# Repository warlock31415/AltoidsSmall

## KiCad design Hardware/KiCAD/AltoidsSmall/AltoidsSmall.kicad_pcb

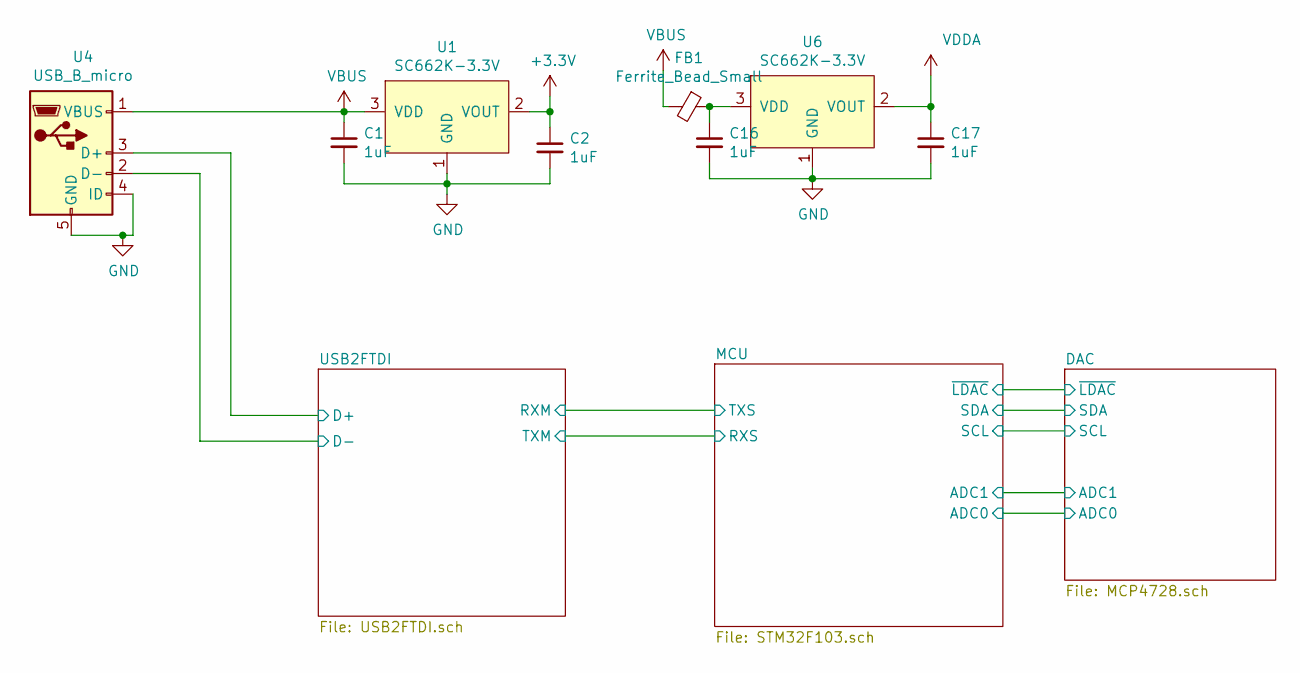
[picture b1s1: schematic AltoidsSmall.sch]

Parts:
C1, C2, C16, C17: 1uF; C_0603_1608Metric_Pad1.05x0.95mm_HandSolder
FB1: Ferrite_Bead_Small; C_0805_2012Metric; Digikey 490-5229-1-ND
U1, U6: SC662K-3.3V; SOT-23
U4: USB_B_micro; USB_Micro-B_PCB

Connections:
/USB2FTDI/D+: U4.3 (D+); also elsewhere on the board
/USB2FTDI/D-: U4.2 (D-); also elsewhere on the board
GND: C1.2, C2.2, C16.2, C17.2, U1.1 (GND), U4.4 (ID), U4.5 (GND), U6.1 (GND); also elsewhere on the board
unnamed: C16.1, FB1.1, U6.3 (VDD)
VBUS: C1.1, FB1.2, U1.3 (VDD), U4.1 (VBUS); also elsewhere on the board
VDDA: C17.1, U6.2 (VOUT); also elsewhere on the board

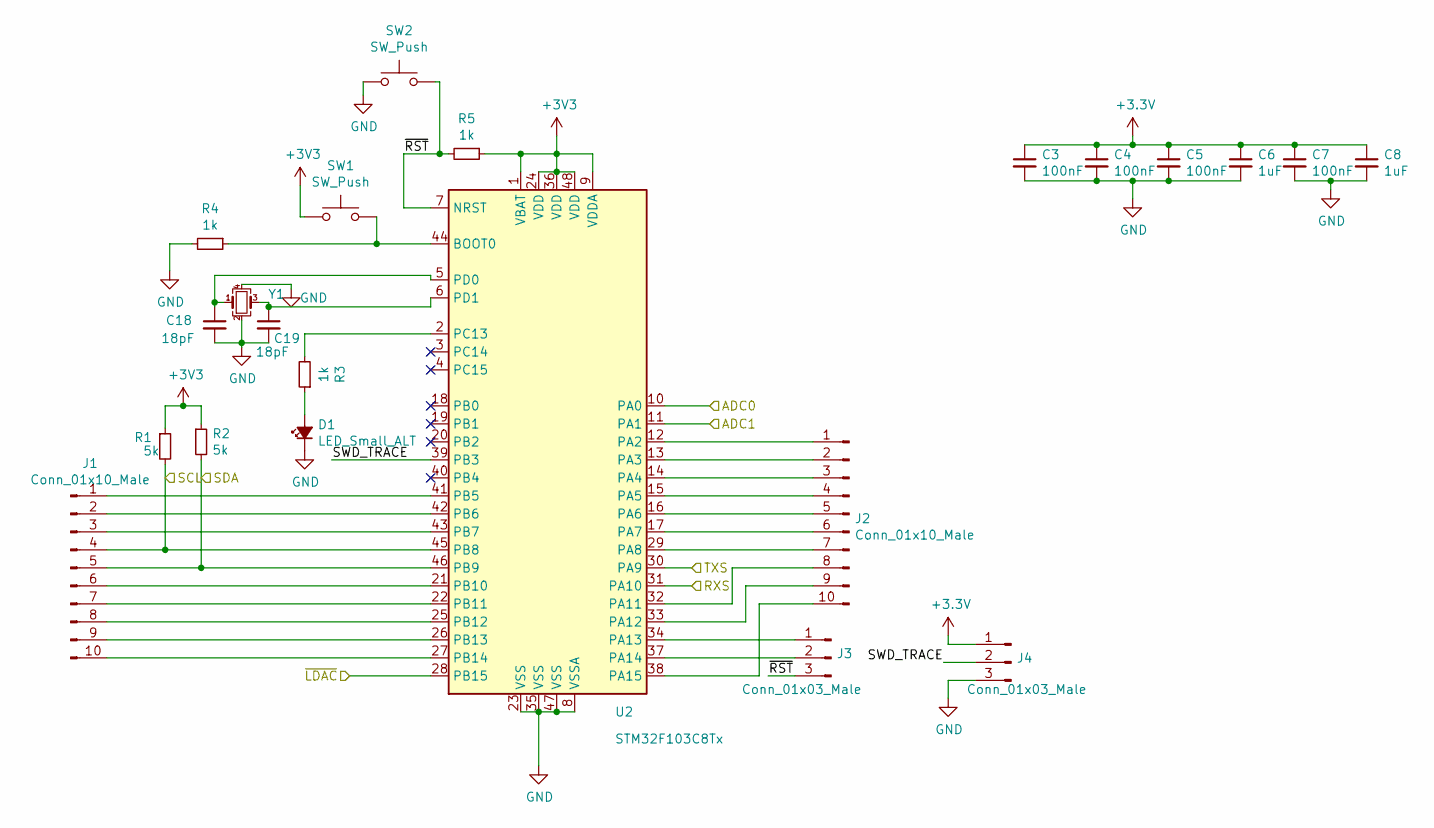
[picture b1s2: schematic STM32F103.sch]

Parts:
C3, C4, C5, C7: 100nF; C_0603_1608Metric_Pad1.05x0.95mm_HandSolder; Digikey 1276-CL10B104KB8VPJCCT-ND
C6, C8: 1uF; C_0603_1608Metric_Pad1.05x0.95mm_HandSolder; Digikey H 5600 2125 50 0001 C CNN
C18, C19: 18pF; C_0603_1608Metric_Pad1.05x0.95mm_HandSolder; Digikey 13-CC0603JRNPO8BN180CT-ND
D1: LED_Small_ALT; D_0603_1608Metric_Castellated; LCSC C193191
J1, J2: Conn_01x10_Male; Conn_Header_1x10_P2.54mm_staggered_0.006in
J3, J4: Conn_01x03_Male; Conn_Header_1x03_P2.54mm_staggered_0.006in
R1, R2: 5k; R_0603_1608Metric_Pad1.05x0.95mm_HandSolder; Digikey CR0603-FX-4991ELFCT-ND
R3, R4, R5: 1k; R_0603_1608Metric_Pad1.05x0.95mm_HandSolder; LCSC C441891
SW1, SW2: SW_Push; SW_Push_1P1T_NO_CK_KMR2
U2: STM32F103C8Tx; LQFP-48_7x7mm_P0.5mm; LCSC C8734
Y1: Crystal_GND24_Small; Crystal_SMD_Abracon_ABM8G-4Pin_3.2x2.5mm; Digikey 50-ECS-80-10-33-CHN-CT-ND

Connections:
/DAC/ADC0: U2.10 (PA0); also elsewhere on the board
/DAC/ADC1: U2.11 (PA1); also elsewhere on the board
/DAC/SCL: J1.4, R1.2, U2.45 (PB8); also elsewhere on the board
/DAC/SDA: J1.5, R2.2, U2.46 (PB9); also elsewhere on the board
/DAC/~LDAC: U2.28 (PB15); also elsewhere on the board
/MCU/RXS: U2.31 (PA10); also elsewhere on the board
/MCU/SWCLK: J3.2, U2.37 (PA14)
/MCU/SWDIO: J3.1, U2.34 (PA13)
/MCU/SWD_TRACE: J4.2, U2.39 (PB3)
/MCU/~RST: J3.3, R5.2, SW2.2, U2.7 (NRST)
/USB2FTDI/RXM: U2.30 (PA9); also elsewhere on the board
GND: C3.2, C4.2, C5.2, C6.2, C7.2, C8.2, C18.2, C19.2, D1.1 (K), J4.3, R4.2, SW2.1, U2.8 (VSSA), U2.23 (VSS), U2.35 (VSS), U2.47 (VSS), Y1.2, Y1.4; also elsewhere on the board
unnamed: C18.1, U2.5 (PD0), Y1.1
unnamed: C19.1, U2.6 (PD1), Y1.3
unnamed: D1.2 (A), R3.1
unnamed: J1.1, U2.41 (PB5)
unnamed: J1.2, U2.42 (PB6)
unnamed: J1.3, U2.43 (PB7)
unnamed: J1.6, U2.21 (PB10)
unnamed: J1.7, U2.22 (PB11)
unnamed: J1.8, U2.25 (PB12)
unnamed: J1.9, U2.26 (PB13)
unnamed: J1.10, U2.27 (PB14)
unnamed: J2.1, U2.12 (PA2)
unnamed: J2.2, U2.13 (PA3)
unnamed: J2.3, U2.14 (PA4)
unnamed: J2.4, U2.15 (PA5)
unnamed: J2.5, U2.16 (PA6)
unnamed: J2.6, U2.17 (PA7)
unnamed: J2.7, U2.29 (PA8)
unnamed: J2.8, U2.32 (PA11)
unnamed: J2.9, U2.33 (PA12)
unnamed: J2.10, U2.38 (PA15)
unnamed: R3.2, U2.2 (PC13)
unnamed: R4.1, SW1.2, U2.44 (BOOT0)

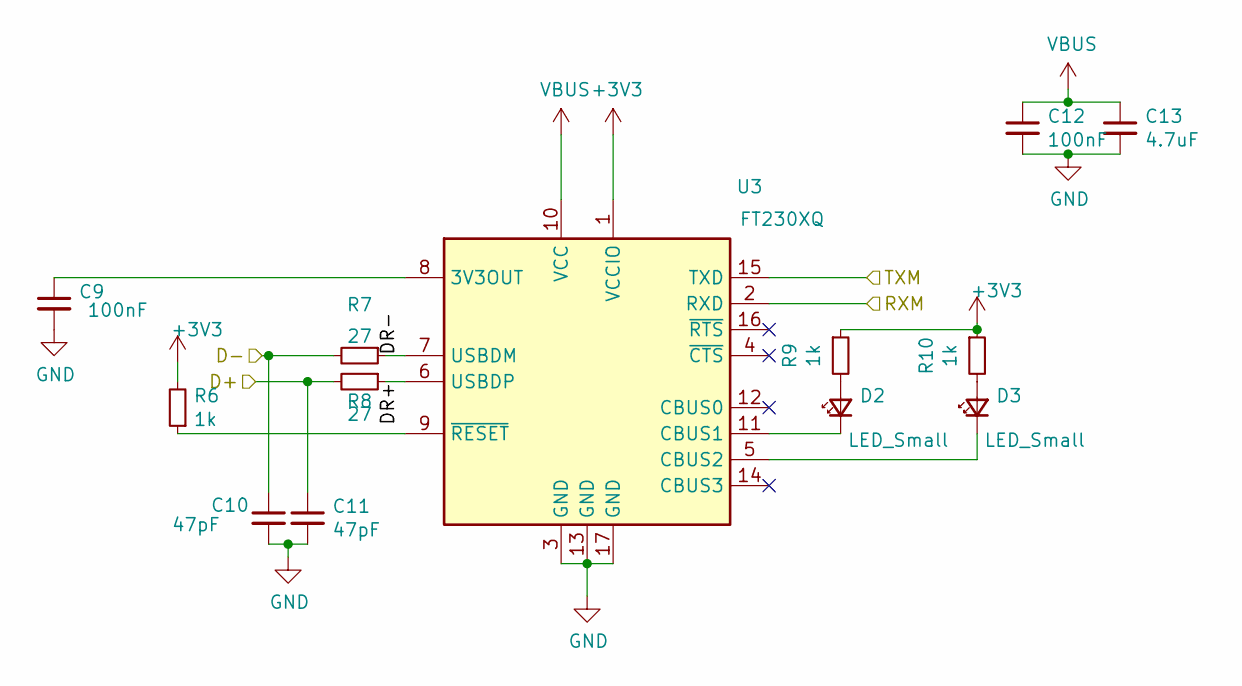
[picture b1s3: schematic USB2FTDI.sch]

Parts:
C9, C12: 100nF; C_0603_1608Metric_Pad1.05x0.95mm_HandSolder; Digikey 1276-CL10B104KB8VPJCCT-ND
C10, C11: 47pF; C_0603_1608Metric_Pad1.05x0.95mm_HandSolder; Digikey 311-4037-1-ND
C13: 4.7uF; C_0805_2012Metric; Digikey 587-2990-1-ND
D2, D3: LED_Small; D_0603_1608Metric_Castellated; Digikey 475-1276-1-ND
R6, R9, R10: 1k; R_0603_1608Metric_Pad1.05x0.95mm_HandSolder
R7, R8: 27; R_0603_1608Metric_Pad1.05x0.95mm_HandSolder; Digikey RR08Q27DCT-ND
U3: FT230XQ; QFN-16-1EP_4x4mm_P0.65mm_EP2.1x2.1mm

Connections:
/MCU/RXS: U3.15 (TXD); also elsewhere on the board
/USB2FTDI/D+: C11.1, R8.2; also elsewhere on the board
/USB2FTDI/D-: C10.1, R7.2; also elsewhere on the board
/USB2FTDI/DR+: R8.1, U3.6 (USBDP)
/USB2FTDI/DR-: R7.1, U3.7 (USBDM)
/USB2FTDI/RXM: U3.2 (RXD); also elsewhere on the board
GND: C9.2, C10.2, C11.2, C12.2, C13.2, U3.3 (GND), U3.13 (GND), U3.17 (GND); also elsewhere on the board
unnamed: C9.1, U3.8 (3V3OUT)
unnamed: D2.1 (K), U3.11 (CBUS1)
unnamed: D2.2 (A), R9.2
unnamed: D3.1 (K), U3.5 (CBUS2)
unnamed: D3.2 (A), R10.2
unnamed: R6.1, U3.9 (~RESET)
VBUS: C12.1, C13.1, U3.10 (VCC); also elsewhere on the board

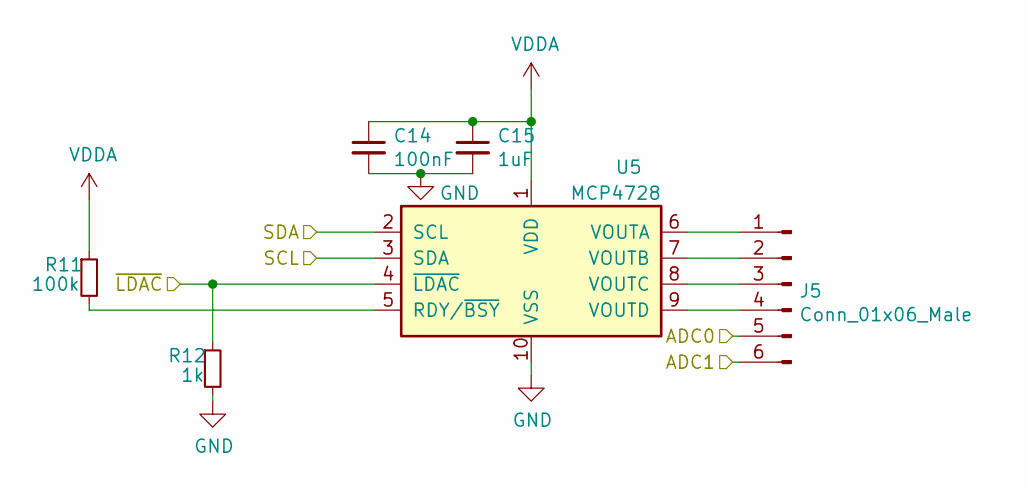
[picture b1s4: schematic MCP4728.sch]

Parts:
C14: 100nF; C_0603_1608Metric_Pad1.05x0.95mm_HandSolder; Digikey 1276-CL10B104KB8VPJCCT-ND
C15: 1uF; C_0603_1608Metric_Pad1.05x0.95mm_HandSolder; Digikey H 5600 2125 50 0001 C CNN
J5: Conn_01x06_Male; Conn_Header_1x06_P2.54mm_staggered_0.006in
R11: 100k; R_0603_1608Metric_Pad1.05x0.95mm_HandSolder; Digikey RMCF0603JT100KCT-ND
R12: 1k; R_0603_1608Metric_Pad1.05x0.95mm_HandSolder; LCSC C441891
U5: MCP4728; MSOP-10_3x3mm_P0.5mm

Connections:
/DAC/ADC0: J5.5; also elsewhere on the board
/DAC/ADC1: J5.6; also elsewhere on the board
/DAC/SCL: U5.3 (SDA); also elsewhere on the board
/DAC/SDA: U5.2 (SCL); also elsewhere on the board
/DAC/~LDAC: R12.1, U5.4 (~LDAC); also elsewhere on the board
GND: C14.2, C15.2, R12.2, U5.10 (VSS); also elsewhere on the board
unnamed: J5.1, U5.6 (VOUTA)
unnamed: J5.2, U5.7 (VOUTB)
unnamed: J5.3, U5.8 (VOUTC)
unnamed: J5.4, U5.9 (VOUTD)
unnamed: R11.2, U5.5 (RDY/~BSY)
VDDA: C14.1, C15.1, R11.1, U5.1 (VDD); also elsewhere on the board

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
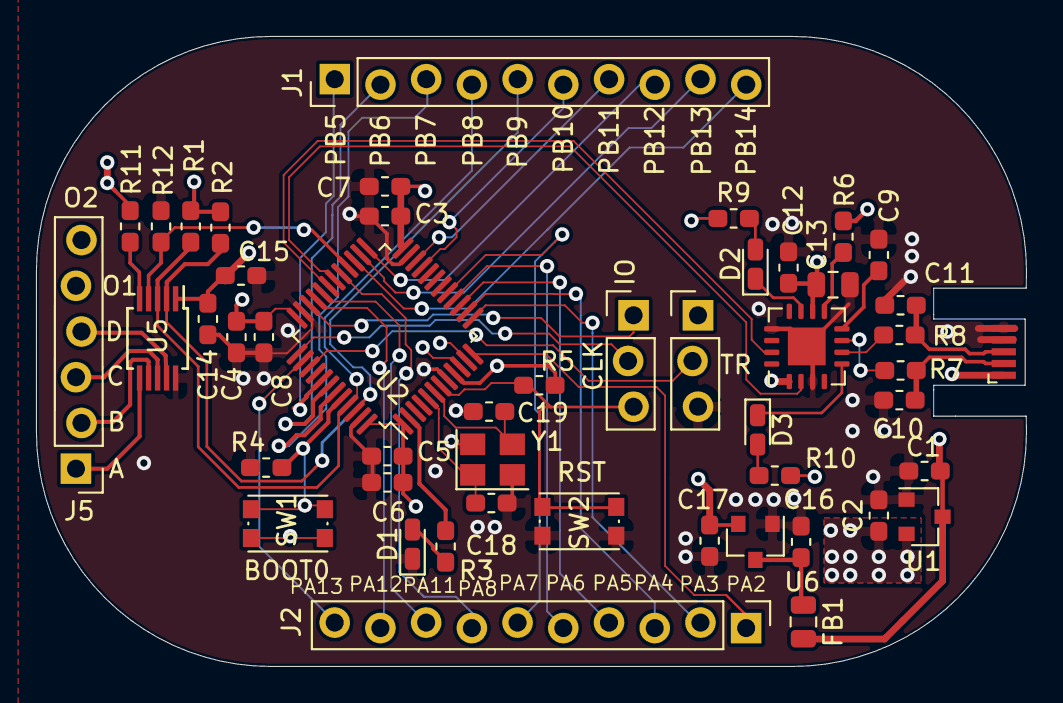
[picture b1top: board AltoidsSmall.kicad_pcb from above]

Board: 4 copper layers, 55.0 x 35.0 mm, 49 parts (0 on the bottom side), 54 nets.

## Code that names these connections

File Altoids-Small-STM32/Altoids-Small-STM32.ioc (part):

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Mcu.Name=STM32F103C(8-B)Tx
Mcu.Package=LQFP48
Mcu.UserName=STM32F103C8Tx
PA0-WKUP.Signal=ADCx_IN0
PA1.Signal=ADCx_IN1
PA10.Mode=Asynchronous
PA10.Signal=USART1_RX
PA13.Mode=Serial_Wire
PA13.Signal=SYS_JTMS-SWDIO
PA14.Mode=Serial_Wire
PA14.Signal=SYS_JTCK-SWCLK
PA9.Mode=Asynchronous
PA9.Signal=USART1_TX
PB8.Mode=I2C
PB8.Signal=I2C1_SCL
PB9.Mode=I2C
PB9.Signal=I2C1_SDA
PD0-OSC_IN.Mode=HSE-External-Oscillator
PD0-OSC_IN.Signal=RCC_OSC_IN
PD1-OSC_OUT.Mode=HSE-External-Oscillator
PD1-OSC_OUT.Signal=RCC_OSC_OUT
RCC.SYSCLKFreq_VALUE=56000000
RCC.SYSCLKSource=RCC_SYSCLKSOURCE_PLLCLK
board=custom

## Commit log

2021-01-10 Added CAMFILES
2021-01-10 Added bom
2021-01-11 Added labels to pins, Added part numbers
